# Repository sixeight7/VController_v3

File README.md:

# VController_v3
Production model of the VController, VC-mini and VC-touch

The VC-touch is a MIDI footcontroller with 15 buttons and a large TFT touch screen:

The VC-mini is a small version of the VController with 3 buttons, 3 LEDs, 2 encoders and 1 LCD display:

The VController is the original controller with 16 buttons, 12 LCDs and 12 LEDs:

All can be fully programmed both onboard and via an external editor for Mac and PC called VC-edit.
All devices share the same code for the Teensy firmware and the editor (Qt)

# Device support
A number of guitar modelers and synths are supported, where it actively read patch names and parameter states for the following devices:
* Fractal Audio Axe-fx 2 (other models may work too, but have not been tested yet)
* Boss GP-10
* Roland GR-55
* Roland VG-99
* Boss Katana (50/100/Artist - MK1 and MK2)
* Boss SY-1000
* Kemper Profiling Amp
* Line 6 Helix (limited)
* Line 6 M13
* Zoom G3
* Zoom MS70-cdr
* Strymon Volante
* TC Electronics G-Major
* NUX MG-300

# General MIDI
The VController, VC-mini and VC-touch are also able to send MIDI PC, CC and Note on/off messages to control any device that is able to receive these messages.

# Programmability
The VController, VC-mini and VC-touch support up to 200 user pages, where a total of almost 3000 commands can be programmed. Any button can execute up to 50 commands.

# Connectivity of the VController
* There are two MIDI in/out conenctors and MIDI 2 doubles as an RRC2 connection for the VG-99.
* Four external expression pedals or eight external switches can be connected.
* One USB slave connector (also used for programming the VController)
* An internal or external Raspberry Pi can add four USB host ports to the VController.

# Connectivity of the VC-mini
* Two 7 pin MIDI connectors with MIDI in/out and power in one connector. MIDI1 has a seperate 7 pin connector with MIDI in/out reversed. The 7 pin connectors are compatible with regular 5 pin MIDI connectors.
* One external expression pedal or two external switches can be connected via a 3.5 mm jack plug (may need an adapter to regular jack.)
* One USB slave connector (also used for programming the VC-mini)
* One USB host port

# Connectivity of the VC-touch
* Three 7 pin MIDI connectors with MIDI in/out and power in one connector, MIDI in/out port on 3,5 mm plugs, wireless MIDI through MIDI BLE and WIFI - AppleMIDI.
* Three external expression pedal or six external switches can be connected via a 3.5 mm jack plug (may need an adapter to regular jack.)
* One USB slave connector (also used for programming the VC-touch)
* One USB host port

# Hardware
This repository contains the building plans (enclosure and schematics) for the VC-mini, the VController and the optional external Raspberry Pi. Check out the building guides for both projects.

# Firmware
This repository also contains the source code for the V-Controller, the VC-mini and for VC-edit. The source code for VC-bridge (the code for the raspberry pi) is in a separate repository called VC-bridge. There are also ready made hex files for the V-Controllers Teensy. There is also special firmware to check hardware of the V-Controller or the VC-mini.

For VC-edit there is a ready to run zip file for windows and dmg-file for Mac. Also the source code of VC-edit is provided.

# Webstore
You can buy ready made VC-mini's and VC-touches or seperate PCBs and enclosures at my webstore.
https://sixeightsoundcontrol.onlineweb.shop/

# Support
Please visit https://www.vguitarforums.com/smf/index.php?board=277.0 for additional information or for any questions you have regarding this project. Please post any questions on the board, where several users and builders can respond and help.

I have invested thousands of hours in this project. You can support me here: https://www.paypal.me/sixeight

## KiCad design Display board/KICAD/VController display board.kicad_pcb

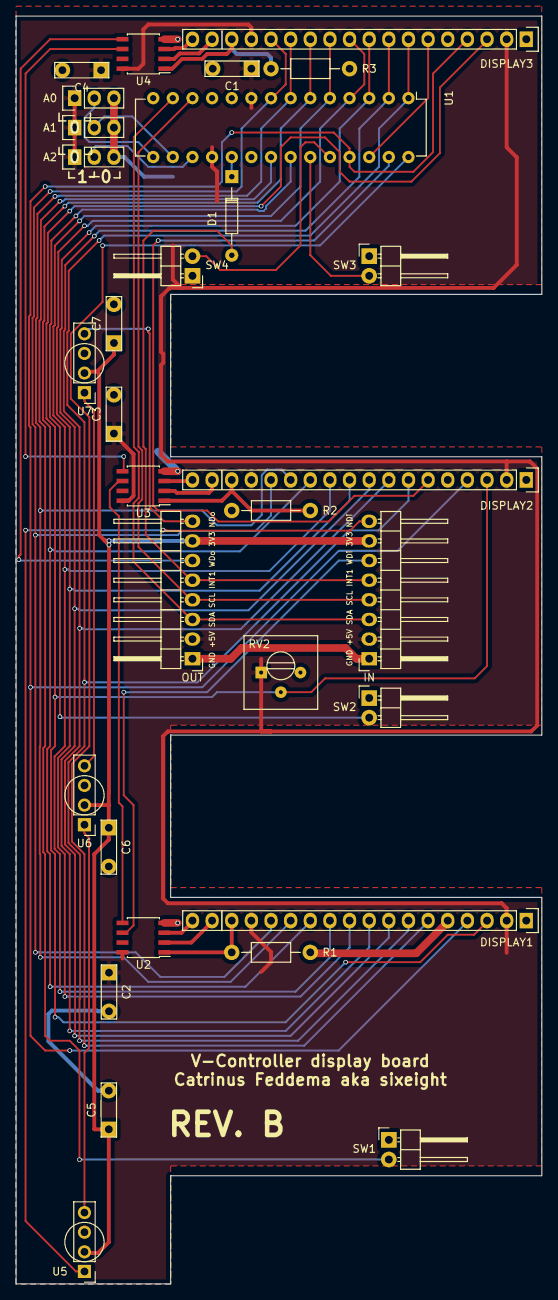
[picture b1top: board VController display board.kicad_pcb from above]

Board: 2 copper layers, 68.0 x 164.0 mm, 31 parts (0 on the bottom side), 44 nets.

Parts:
A0, A1, A2: JUMPER3; Pin_Header_Straight_1x03
C1, C2, C3, C4, C5, C6, C7: 100n; C_small_CF
D1: D; Diode_DO-35_SOD27_Horizontal_RM10
DISPLAY1, DISPLAY2, DISPLAY3: LCD16X2RGB; Socket_Strip_Straight_1x18
P1: IN; Pin_Header_Angled_1x08
P2: OUT; Pin_Header_Angled_1x08
R1, R2, R3: 220; Resistor_Horizontal_RM10mm
RV2: POT; Potentiometer_Trimmer-Suntan-TSR-3386P
SW1, SW2, SW3, SW4: SW_PUSH; Pin_Header_Angled_1x02
U1: MCP23017; DIP-28_W7.62mm
U2, U3, U4: WS2811; SOIC-8_3.9x4.9mm_Pitch1.27mm
U5, U6, U7: NEOPIXEL_LED; NeoPixel_CF

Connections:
+3V3: C5.1, C6.1, C7.1, P1.7, P2.7, U5.2, U6.2, U7.2
+5V: A0.1, A1.1, A2.1, C1.1, C2.1, C3.1, C4.1, DISPLAY1.2, DISPLAY1.15, DISPLAY2.2, DISPLAY2.15, DISPLAY3.2, DISPLAY3.15, P1.2, P2.2, RV2.1, U1.9, U1.18, U2.8, U3.8, U4.8
GND: A0.3, A1.3, A2.3, C1.2, C2.2, C3.2, C4.2, C5.2, C6.2, C7.2, DISPLAY1.1, DISPLAY1.5, DISPLAY2.1, DISPLAY2.5, DISPLAY3.1, DISPLAY3.5, P1.1, P2.1, R1.2, R2.2, R3.2, RV2.3, SW1.1, SW2.1, SW3.1, SW4.1, U1.10, U2.4, U3.4, U4.4, U5.3, U6.3, U7.3
unnamed: A0.2, U1.15
unnamed: A1.2, U1.16
unnamed: A2.2, U1.17
unnamed: D1.1, U1.19
unnamed: D1.2, P1.5, P2.5
unnamed: DISPLAY1.3, DISPLAY2.3, DISPLAY3.3, RV2.2
unnamed: DISPLAY1.4, DISPLAY2.4, DISPLAY3.4, U1.25
unnamed: DISPLAY1.6, U1.28
unnamed: DISPLAY1.7, DISPLAY2.7, DISPLAY3.7, U1.1
unnamed: DISPLAY1.8, DISPLAY2.8, DISPLAY3.8, U1.2
unnamed: DISPLAY1.9, DISPLAY2.9, DISPLAY3.9, U1.3
unnamed: DISPLAY1.10, DISPLAY2.10, DISPLAY3.10, U1.4
unnamed: DISPLAY1.11, DISPLAY2.11, DISPLAY3.11, U1.5
unnamed: DISPLAY1.12, DISPLAY2.12, DISPLAY3.12, U1.6
unnamed: DISPLAY1.13, DISPLAY2.13, DISPLAY3.13, U1.7
unnamed: DISPLAY1.14, DISPLAY2.14, DISPLAY3.14, U1.8
unnamed: DISPLAY1.16, R1.1, U2.1
unnamed: DISPLAY1.17, U2.2
unnamed: DISPLAY1.18, U2.3
unnamed: DISPLAY2.6, U1.27
unnamed: DISPLAY2.16, R2.1, U3.1
unnamed: DISPLAY2.17, U3.2
unnamed: DISPLAY2.18, U3.3
unnamed: DISPLAY3.6, U1.26
unnamed: DISPLAY3.16, R3.1, U4.1
unnamed: DISPLAY3.17, U4.2
unnamed: DISPLAY3.18, U4.3
unnamed: P1.3, P2.3, U1.13
unnamed: P1.4, P2.4, U1.12
unnamed: P1.6, U2.6
unnamed: P1.8, U5.1
unnamed: P2.6, U4.5
unnamed: P2.8, U7.4
unnamed: SW1.2, U1.21
unnamed: SW2.2, U1.22
unnamed: SW3.2, U1.23
unnamed: SW4.2, U1.24
unnamed: U2.5, U3.6
unnamed: U3.5, U4.6
unnamed: U5.4, U6.1
unnamed: U6.4, U7.1

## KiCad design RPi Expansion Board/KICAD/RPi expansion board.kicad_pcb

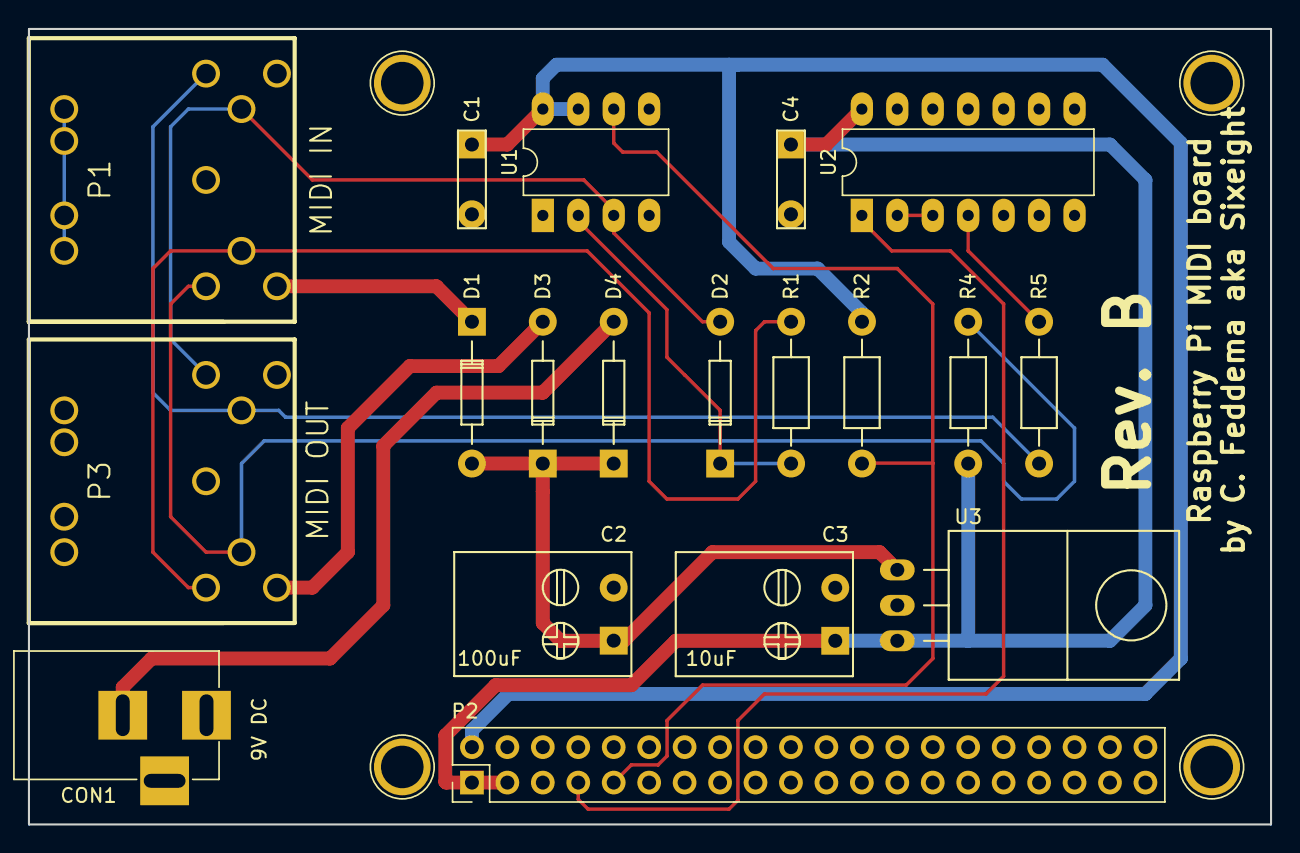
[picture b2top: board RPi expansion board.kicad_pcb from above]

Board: 2 copper layers, 89.0 x 57.0 mm, 19 parts (0 on the bottom side), 16 nets.

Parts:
C1, C4: 100n; C_small_CF
C2: 100uF; C_Radial_FLAT
C3: 10uF; C_Radial_FLAT
CON1: 9V DC; BARREL_JACK
D1, D2, D3, D4: D; Diode_DO-35_SOD27_Horizontal_RM10
P1: MIDI IN; DIN_7_CF
P2: GPIO; Pin_Header_Straight_2x20_Pitch2.54mm
P3: MIDI OUT; DIN_7_CF
R1, R4, R5: 220; Resistor_Horizontal_RM10mm
R2: 4k7; Resistor_Horizontal_RM10mm
U1: 6N138; DIP-8_W7.62mm_LongPads
U2: 74HC14; DIP-14_W7.62mm_LongPads
U3: LM7805CT; TO-220_Flat_CF

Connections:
+3V3: C1.1, P2.2, R2.2, U1.7, U1.8
+5V: C3.1, C4.1, P2.1, P2.3, R4.1, U2.14, U3.3
+9V: C2.1, D1.2, D3.1, D4.1, U3.1
GND: C1.2, C2.2, C3.2, C4.2, CON1.1, P1.7, P2.5, P2.10, P2.13, P2.19, P2.26, P2.29, P2.33, P2.40, P3.2, P3.7, P3.8, U1.5, U2.5, U2.7, U2.9, U2.11, U2.13, U3.2
MRX+: P1.4, P3.1, R1.2
MRX-: D2.2, P1.5, P3.3, U1.3
MTX+: P1.1, P3.4, R4.2
MTX-: P1.3, P3.5, R5.2
unnamed: CON1.2, D4.2
unnamed: D1.1, P1.6
unnamed: D2.1, R1.1, U1.2
unnamed: D3.2, P3.6
unnamed: R5.1, U2.4
unnamed: U2.2, U2.3
RX: P2.9, R2.1, U1.6
TX: P2.7, U2.1

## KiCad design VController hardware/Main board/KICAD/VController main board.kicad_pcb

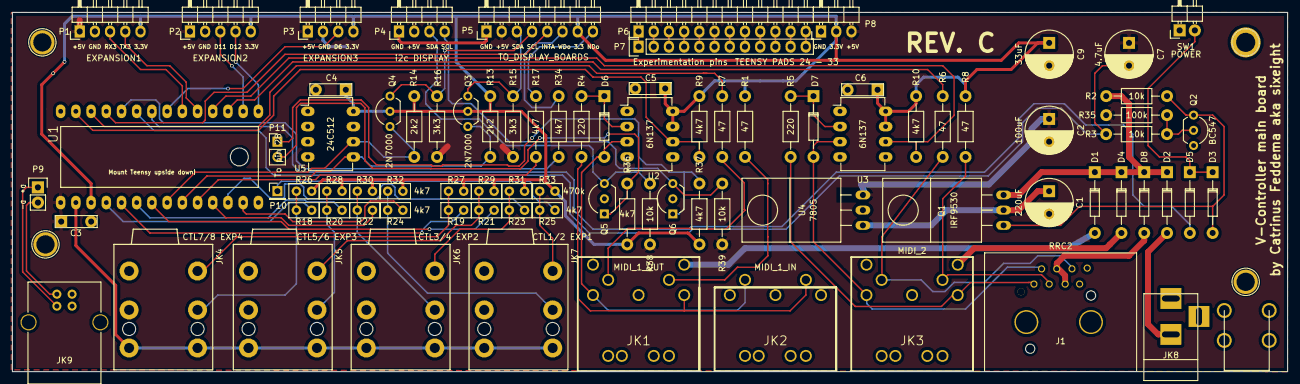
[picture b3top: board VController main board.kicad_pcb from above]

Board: 2 copper layers, 213.0 x 60.0 mm, 87 parts (0 on the bottom side), 77 nets.

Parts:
C1: 220uF; C_Radial_D8_L13_P3.8
C2: 100uF; C_Radial_D8_L13_P3.8
C3, C4, C5, C6: 100n; C_small_CF
C7: 4.7uF; C_Radial_D8_L13_P3.8
C9: 33uF; C_Radial_D8_L13_P3.8
D1, D2, D4, D8: 1N5817; Diode_DO-35_SOD27_Horizontal_RM10
D3, D5, D6, D7: D; Diode_DO-35_SOD27_Horizontal_RM10
J1: RRC2; Neutrik_Ethercon_NE8FBH-S_CF
JK1: MIDI_1_OUT; DIN_7_CF
JK2: MIDI_1_IN; DIN_5_CF
JK3: MIDI_2; DIN_7_CF
JK4: CTL7/8 EXP4; NEUTRIK_NRJ6HF
JK5: CTL5/6 EXP3; NEUTRIK_NRJ6HF
JK6: CTL3/4 EXP2; NEUTRIK_NRJ6HF
JK7: CTL1/2 EXP1; NEUTRIK_NRJ6HF
JK8: DC POWER; BARREL_JACK
JK9: USB_B
P1: EXPANSION1; Pin_Header_Angled_1x05
P2: EXPANSION2; Pin_Header_Angled_1x05
P3: EXPANSION3; Pin_Header_Angled_1x04
P4: i2c DISPLAY; Pin_Header_Angled_1x04
P5: TO_DISPLAY_BOARDS; Pin_Header_Angled_1x08
P6: Experimentation pins; Pin_Header_Angled_1x12
P7: TEENSY PADS 24 - 33; Pin_Header_Straight_1x12
P8: CONN_01X03; Pin_Header_Angled_1x03
P9: D+/D-; Pin_Header_Straight_1x02
P10: To pin 28; Pin_Header_Straight_1x01_Pitch2.54mm
P11: SDA/SCL; Pin_Header_Straight_1x02_Pitch2.54mm
P13: PCB HOLDER M3; PCB_HOLDER_M3
Q1: IRF9530; TO-220_Flat_CF
Q2: BC547; TO-92_Inline_Wide
Q3, Q4, Q5, Q6: 2N7000; TO-92_Inline_Wide
R1, R6, R7, R8: 47; Resistor_Horizontal_RM10mm
R2, R3, R38, R39: 10k; Resistor_Horizontal_RM10mm
R4, R5: 220; Resistor_Horizontal_RM10mm
R9, R10, R17, R34, R36, R37: 4k7; Resistor_Horizontal_RM10mm
R13, R14: 2k2; Resistor_Horizontal_RM10mm
R15, R16: 3k3; Resistor_Horizontal_RM10mm
R18, R19, R20, R21, R22, R23, R24, R25, R26, R28, R30, R32: 4k7; RESISTOR_NETWORK
R27, R29, R31, R33: 470k; RESISTOR_NETWORK
R35: 100k; Resistor_Horizontal_RM10mm
SW1: POWER; Pin_Header_Angled_1x02
U1: Teensy_3.2; Teensy-3.1_CF_oval_pads_reversed
U2, U3: 6N137; DIP-8_W7.62mm_LongPads
U4: 7805; TO-220_Flat_CF
U5: 24C512; DIP-8_W7.62mm_LongPads

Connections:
+3V3: C4.1, C5.1, C6.1, C9.1, P1.5, P2.5, P3.4, P5.7, P8.2, Q3.2, Q4.2, R1.1, R8.1, R9.1, R10.1, R13.1, R14.1, R26.2, R27.2, R28.2, R29.2, R30.2, R31.2, R32.2, R33.2, R36.2, R37.2, U1.24, U2.7, U2.8, U3.7, U3.8, U5.8
+5V: C2.1, C3.1, C7.1, P1.1, P2.1, P3.1, P4.2, P5.2, P8.3, R15.1, R16.1, R35.1, R38.1, R39.1, U1.26, U4.3
+9V: D1.1, D2.1, D4.1, D8.1, Q1.3, R2.1
/SCL: P5.4, Q4.3, R16.2
/SDA: P5.3, Q3.3, R15.2
GND: C1.2, C2.2, C3.2, C4.2, C5.2, C6.2, C9.2, J1.7, J1.8, J1.9, JK1.2, JK1.7, JK1.8, JK3.2, JK3.7, JK3.8, JK8.1, JK9.4, JK9.5, P1.2, P2.2, P3.2, P4.1, P5.1, P8.1, P13.1, Q2.3, SW1.1, U1.27, U2.5, U3.5, U4.2, U5.1, U5.2, U5.3, U5.4, U5.7
GNDA: JK4.S, JK4.S-, JK5.S, JK5.S-, JK6.S, JK6.S-, JK7.S, JK7.S-, U1.25
INTA: P5.5, U1.2
NEO: P5.8, R17.1
NEO2: R34.2, U1.3
unnamed: C1.1, Q1.2, U4.1
unnamed: D1.2, JK1.6
unnamed: D2.2, JK8.2
unnamed: D3.1, D5.1, SW1.2
unnamed: D3.2, Q1.1, Q2.1, R2.2
unnamed: D4.2, JK3.6
unnamed: D6.1, R4.1, U2.2
unnamed: D6.2, JK1.3, JK2.5, U2.3
unnamed: D7.1, R5.1, U3.2
unnamed: D7.2, J1.2, JK3.3, U3.3
unnamed: D8.2, J1.4, J1.5
unnamed: J1.1, JK3.1, R5.2
unnamed: J1.3, JK3.4, R8.2
unnamed: J1.6, JK3.5, R6.2
unnamed: JK1.1, JK2.4, R4.2
unnamed: JK1.4, R1.2
unnamed: JK1.5, R7.2
unnamed: JK4.R, R18.1, R26.1
unnamed: JK4.T, R19.1, R27.1
unnamed: JK5.R, R20.1, R28.1
unnamed: JK5.T, R21.1, R29.1
unnamed: JK6.R, R22.1, R30.1
unnamed: JK6.T, R23.1, R31.1
unnamed: JK7.R, R24.1, R32.1
unnamed: JK7.T, R25.1, R33.1
unnamed: JK9.2, P9.2
unnamed: JK9.3, P9.1
unnamed: P1.3, U1.7
unnamed: P1.4, U1.8
unnamed: P2.3, U1.11
unnamed: P2.4, U1.12
unnamed: P3.3, U1.6
unnamed: P4.3, Q5.3, R38.2
unnamed: P4.4, Q6.3, R39.2
unnamed: P5.6, R34.1
unnamed: P6.1, P7.1
unnamed: P6.2, P7.2
unnamed: P6.3, P7.3
unnamed: P6.4, P7.4
unnamed: P6.5, P7.5
unnamed: P6.6, P7.6
unnamed: P6.7, P7.7
unnamed: P6.8, P7.8
unnamed: P6.9, P7.9
unnamed: P6.10, P7.10
unnamed: P6.11, P7.11
unnamed: P6.12, P7.12
unnamed: P10.1, R25.2
unnamed: P11.1, Q6.1, R37.1
unnamed: P11.2, Q5.1, R36.1
unnamed: Q2.2, R3.2, R35.2
unnamed: R6.1, U1.10
unnamed: R7.1, U1.1
unnamed: R9.2, U1.0, U2.6
unnamed: R10.2, U1.9, U3.6
unnamed: R17.2, U1.17
unnamed: R18.2, U1.23
unnamed: R19.2, U1.22
unnamed: R20.2, U1.21
unnamed: R21.2, U1.20
unnamed: R22.2, U1.16
unnamed: R23.2, U1.15
unnamed: R24.2, U1.14
POWER: C7.2, R3.1, U1.4
POWER_SW: D5.2, U1.5
SCL3.3: Q4.1, R14.2, U1.19, U5.6
SDA3.3: Q3.1, R13.2, U1.18, U5.5

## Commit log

2017-03-23 :neckbeard: Added .gitattributes & .gitignore files
2017-03-23 Publish building plans
2017-03-23 Sketch for testing hardware
2017-03-23 First version
    Still work in progress,,,
2017-04-09 Updated resistors in display board
2017-09-04 Updated schematics, boards and guide
2017-09-04 Added Rpi case
2017-09-06 Added Protel gerbers and KICAD files
2017-09-16 Improved hardware test sketch
2017-09-23 Updated BOM and power option
2017-09-23 Updated BOM again
2017-09-27 Added compiled version 3.0.1
2017-10-04 Added bass mode patches
2017-10-05 Added 3 and 4 string bass mode patches
2017-10-13 Uploaded correct version
2017-10-24 First commit of v3
2017-10-29 Easier to bend bracket
2017-10-29 Added labels
2017-10-29 Updated guide
2017-11-05 Firmware v3.0.2
2017-11-05 Upload user manual
2018-09-10 Create README.md
    Added README.md
2018-09-22 VController V3.1 and VC-edit
2018-11-22 Version 1.1
    Added missing diodes in BOM.
2018-11-22 Updated user manual for version 3.2
2018-11-22 BOM updated
2019-09-09 Firmware v3.3
    Now support for the new VC-mini hardware. Added Teensy 3.6 USB Host
    support, encoders, dual switch press support, MIID controllable switches
    and much more.
2019-09-09 Firmware 3.3 for VController and VC-mini
2019-09-09 New test sketch for VC-mini
2019-09-09 VC-edit v1.2 for Vcontroller/VC-mini v3.3
    Source code and compiled binaries for both Windows and Mac
2019-09-09 VC-mini hardware
    Enclosure and schematic of the VC-mini
2019-09-09 Updated building plans for VController and VC-mini
2019-09-10 Typo removed
2019-09-21 Updated manual
2019-09-23 Manual updated
2019-09-29 Firmware 3.3.1 - Improved encoder support for VC-mini
2019-09-30 Updated BOM
2019-10-02 Main board rev. D
    Fixed Q5/Q6 not having 3.3V on center pin.
2019-10-26 New version
2019-10-28 Updated part links and video's
2020-01-04 Updated enclosure for VC-mini
2020-01-04 Updated building guide with new enclosure
2020-01-04 Updated building guide with new Buydisplay options
2020-01-04 Added new display options from BuyDisplay
2020-01-04 Added alternative option for enclosure
2020-01-08 Removed RGB option of buydisplay
2020-01-08 Removed RGB disply option of buydisplay
2020-01-20 Release of firmware v.3.4.0
2020-01-20 Release VC-edit v.3.4.0
2020-02-13 Removed old stl for Adafruit display
2020-06-02 Upload firmware 3.5.0
2020-06-02 VC-edit 3_5_0 released
2020-07-20 VC-edit 3.5.0 for windows released
2020-11-30 Release of firmware 3.6.1
    Added support for the NUX MG-300 and the Katana MK2
2020-11-30 VC-edit 3.6.1
2020-11-30 Updated user manual for v3.6.1
2020-11-30 version 3.6.1 VC-mini
2021-04-13 Release of firmware 3.7.0
2021-04-13 Release firmware 3.7.0
2021-04-18 The old library
2021-04-19 For firmware v3.7.0
    Fixed crash
2021-04-24 Release 3.7.1
2021-05-17 Updated manual for firmware 3.7.2
2021-05-20 Solving inconsistent file location and naming
2021-05-20 Release of firmware 3.7.2
2021-05-20 Release VC-edit 3.7.1
2021-05-24 Release of FW3.7.3 for VC-mini
2021-06-07 VC-edit FW3.71
2021-07-22 Quick fix - patch saving
2022-03-12 Release firmware 3.9.0
2022-03-12 Release 3.9.0
2022-03-15 VC-touch hardware upload
2022-04-18 VC-touch window
2022-04-23 Create VC-edit v3_9_1.dmg
    Compiled with Qt 6.3
2022-04-24 Release v3.9.1
    Now uses QC 6.3
2022-05-02 Release of VCtouch wireless v1.0.0
2022-05-03 Updated documentation
2022-05-04 Updated stl's for display
2022-05-16 Adding building guides to hardware folders
2022-05-16 Added building guide for VC-touch
2022-10-24 Release firmware 3.10
2022-10-24 Release VC-edit firmware 3.10
2022-12-05 Release firmware 3.10.2
2022-12-05 Updated manual for firmware 3.10.2
2023-03-20 Release of firmware 3.11.0
2023-10-25 Updated VC-touch hardware
2023-10-25 Updated building guides
2023-10-26 VController modification for Teensy 4.1
2023-11-21 Release firmwre 3_12_0
2023-12-02 Release VC-edit v3.12.0
2023-12-03 Manual for firmware 3.12.0
2024-01-02 Release of firmware 3.12.1
